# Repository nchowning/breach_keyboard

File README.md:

# Breach Split Keyboard

This is a hobby project to create a keyboard that fits my needs. I figured why not share my progress.

## Firmware

On this, I took the lazy way out after finding an online firmware builder - [Keyboard Firmware Builder](http://kbfirmware.com/). This thing is awesome. You point it at a [keyboard-layout-editor.com](https://www.keyboard-layout-editor.com) layout, tweak the settings, then it spits out a compiled .hex file (or the [qmk](https://qmk.fm) source if you want). In this repo, I'm including the keyboard-layout-editor json file as well as the Keyboard Firmware Builder config json file. You can just upload that config & have Keyboard Firmware Builder deliver a hex file for you. In the future I might include the qmk source in this repo but I won't bother for now.

Since this keyboard uses a pro micro for each half, the firmware flashing process is a little bit different than if you'd used a teensy 2.0. I've added a reset tact switch so that you can easily program it. Just quickly hit the reset button twice & then fire off something like this:

```
avrdude -p atmega32u4 -P /dev/ttyACM0  -c avr109 -U flash:w:breach-left.hex
```

`/dev/ttyACM0` might be different on your machine so keep that in mind.

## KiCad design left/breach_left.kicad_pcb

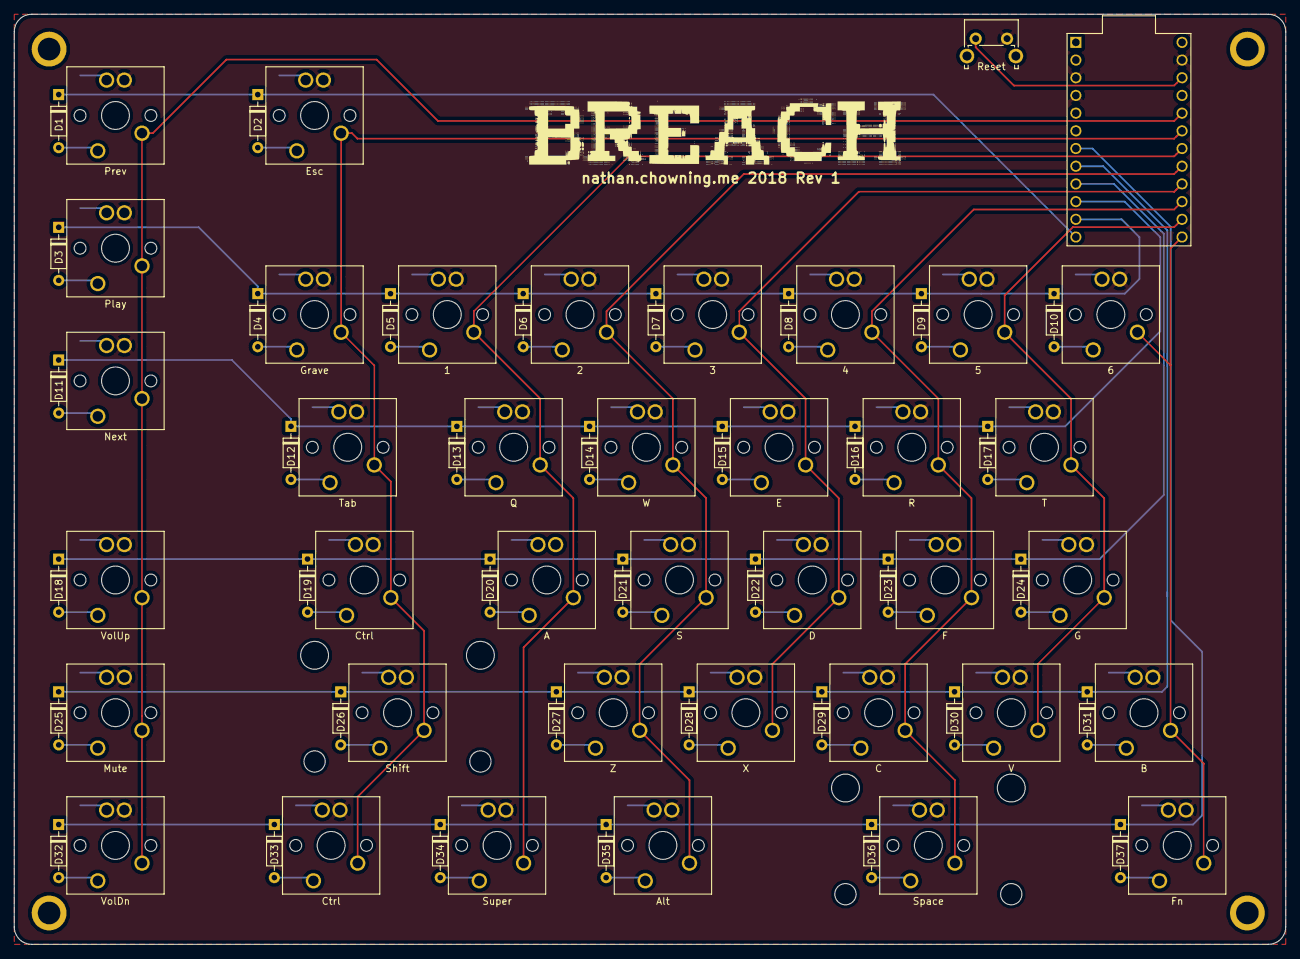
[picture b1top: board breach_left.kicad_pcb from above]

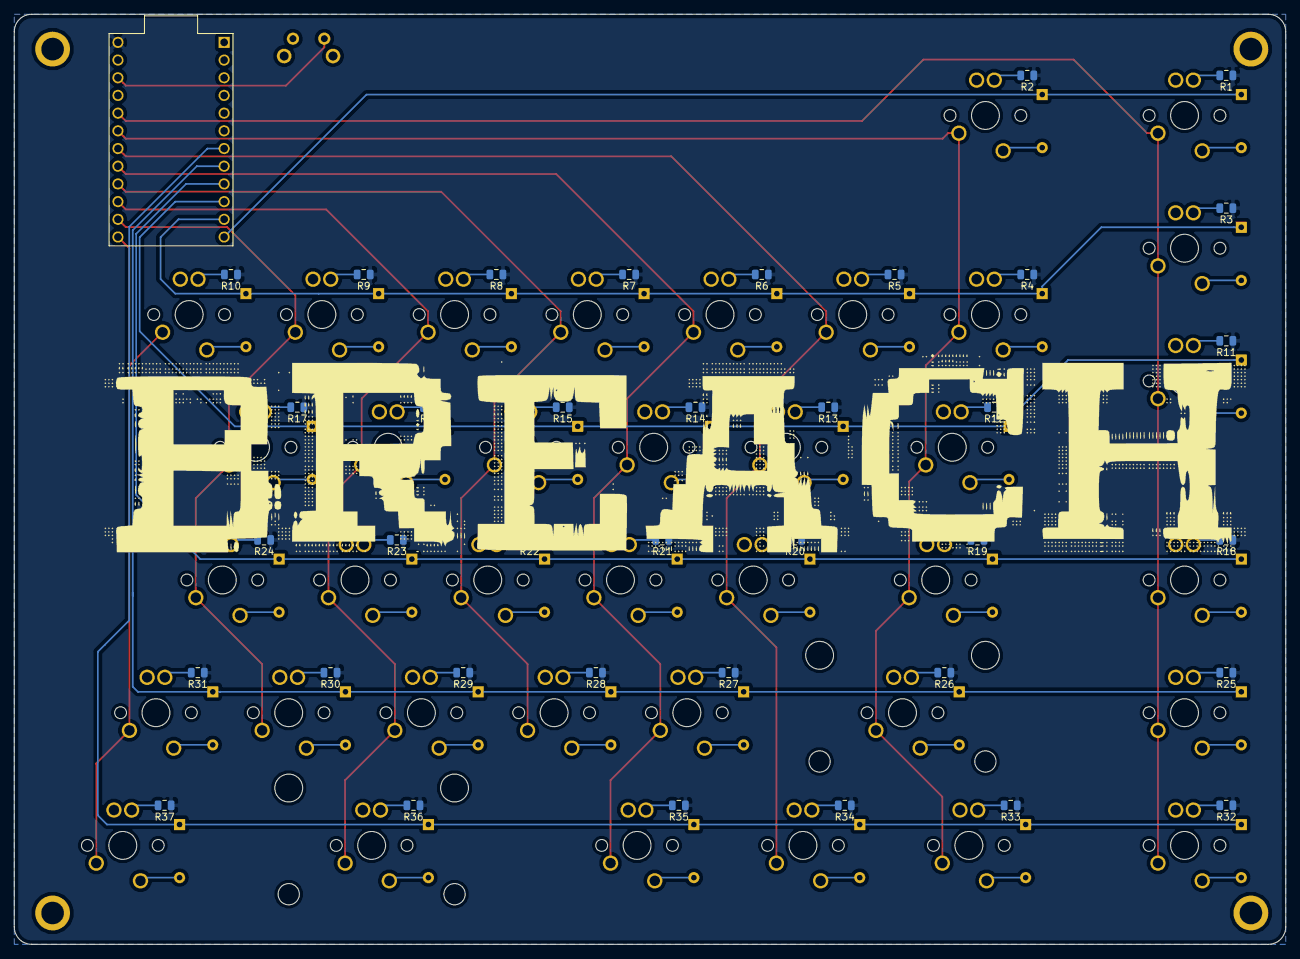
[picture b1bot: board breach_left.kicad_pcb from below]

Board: 2 copper layers, 182.5 x 133.5 mm, 113 parts (37 on the bottom side), 91 nets.

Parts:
D1, D2, D3, D4, D5, D6, D7, D8, D9, D10, D11, D12, D13, D14, D15, D16, D17, D18, D19, D20, D21, D22, D23, D24, D25, D26, D27, D28, D29, D30, D31, D32, D33, D34, D35, D36, D37: 1N4148; D_DO-35_SOD27_P7.62mm_Horizontal
R1, R2, R3, R4, R5, R6, R7, R8, R9, R10, R11, R12, R13, R14, R15, R16, R17, R18, R19, R20, R21, R22, R23, R24, R25, R26, R27, R28, R29, R30, R31, R32, R33, R34, R35, R36, R37: R_Small_US; R_0805_2012Metric
SW1, SW2, SW3, SW4, SW5, SW6, SW7, SW8, SW9, SW10, SW11, SW12, SW13, SW14, SW15, SW16, SW17, SW18, SW19, SW20, SW21, SW22, SW23, SW24, SW25, SW27, SW28, SW29, SW30, SW31, SW32, SW33, SW34, SW35, SW37: SW_Push_LED; SW_Cherry_MX1A_1.00u_PCB
SW26: SW_Push_LED; SW_Cherry_MX1A_2.25u_PCB
SW36: SW_Push_LED; SW_Cherry_MX1A_2.75u_PCB
SW38: SW_Push; SW_Tactile_SPST_Angled_PTS645Vx39-2LFS
U1: ProMicro

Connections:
5V: R1.1, R2.1, R3.1, R4.1, R5.1, R6.1, R7.1, R8.1, R9.1, R10.1, R11.1, R12.1, R13.1, R14.1, R15.1, R16.1, R17.1, R18.1, R19.1, R20.1, R21.1, R22.1, R23.1, R24.1, R25.1, R26.1, R27.1, R28.1, R29.1, R30.1, R31.1, R32.1, R33.1, R34.1, R35.1, R36.1, R37.1, U1.24
COL1: SW1.2, SW3.2, SW11.2, SW18.2, SW25.2, SW32.2, U1.20
COL2: SW2.2, SW4.2, SW12.2, SW19.2, SW26.2, SW33.2, U1.19
COL3: SW5.2, SW13.2, SW20.2, SW34.2, U1.18
COL4: SW6.2, SW14.2, SW21.2, SW27.2, SW35.2, U1.17
COL5: SW7.2, SW15.2, SW22.2, SW28.2, U1.16
COL6: SW8.2, SW16.2, SW23.2, SW29.2, SW36.2, U1.15
COL7: SW9.2, SW17.2, SW24.2, SW30.2, U1.14
COL8: SW10.2, SW31.2, SW37.2, U1.13
GND: SW1.3, SW2.3, SW3.3, SW4.3, SW5.3, SW6.3, SW7.3, SW8.3, SW9.3, SW10.3, SW11.3, SW12.3, SW13.3, SW14.3, SW15.3, SW16.3, SW17.3, SW18.3, SW19.3, SW21.3, SW22.3, SW23.3, SW24.3, SW25.3, SW26.3, SW27.3, SW28.3, SW29.3, SW30.3, SW31.3, SW32.3, SW33.3, SW34.3, SW35.3, SW36.3, SW37.3, SW38.2, U1.3, U1.4, U1.23
unnamed: D1.2, SW1.1
unnamed: D2.2, SW2.1
unnamed: D3.2, SW3.1
unnamed: D4.2, SW4.1
unnamed: D5.2, SW5.1
unnamed: D6.2, SW6.1
unnamed: D7.2, SW7.1
unnamed: D8.2, SW8.1
unnamed: D9.2, SW9.1
unnamed: D10.2, SW10.1
unnamed: D11.2, SW11.1
unnamed: D12.2, SW12.1
unnamed: D13.2, SW13.1
unnamed: D14.2, SW14.1
unnamed: D15.2, SW15.1
unnamed: D16.2, SW16.1
unnamed: D17.2, SW17.1
unnamed: D18.2, SW18.1
unnamed: D19.2, SW19.1
unnamed: D20.2, SW20.1
unnamed: D21.2, SW21.1
unnamed: D22.2, SW22.1
unnamed: D23.2, SW23.1
unnamed: D24.2, SW24.1
unnamed: D25.2, SW25.1
unnamed: D26.2, SW26.1
unnamed: D27.2, SW27.1
unnamed: D28.2, SW28.1
unnamed: D29.2, SW29.1
unnamed: D30.2, SW30.1
unnamed: D31.2, SW31.1
unnamed: D32.2, SW32.1
unnamed: D33.2, SW33.1
unnamed: D34.2, SW34.1
unnamed: D35.2, SW35.1
unnamed: D36.2, SW36.1
unnamed: D37.2, SW37.1
unnamed: R1.2, SW1.4
unnamed: R2.2, SW2.4
unnamed: R3.2, SW3.4
unnamed: R4.2, SW4.4
unnamed: R5.2, SW5.4
unnamed: R6.2, SW6.4
unnamed: R7.2, SW7.4
unnamed: R8.2, SW8.4
unnamed: R9.2, SW9.4
unnamed: R10.2, SW10.4
unnamed: R11.2, SW11.4
unnamed: R12.2, SW12.4
unnamed: R13.2, SW13.4
unnamed: R14.2, SW14.4
unnamed: R15.2, SW15.4
unnamed: R16.2, SW16.4
unnamed: R17.2, SW17.4
unnamed: R18.2, SW18.4
unnamed: R19.2, SW19.4
unnamed: R20.2, SW20.4
unnamed: R21.2, SW21.4
unnamed: R22.2, SW22.4
unnamed: R23.2, SW23.4
unnamed: R24.2, SW24.4
unnamed: R25.2, SW25.4
unnamed: R26.2, SW26.4
unnamed: R27.2, SW27.4
unnamed: R28.2, SW28.4
unnamed: R29.2, SW29.4
unnamed: R30.2, SW30.4
unnamed: R31.2, SW31.4
unnamed: R32.2, SW32.4
unnamed: R33.2, SW33.4
unnamed: R34.2, SW34.4
unnamed: R35.2, SW35.4
unnamed: R36.2, SW36.4
unnamed: R37.2, SW37.4
ROW1: D1.1, D2.1, U1.12
ROW2: D3.1, D4.1, D5.1, D6.1, D7.1, D8.1, D9.1, D10.1, U1.11
ROW3: D11.1, D12.1, D13.1, D14.1, D15.1, D16.1, D17.1, U1.10
ROW4: D18.1, D19.1, D20.1, D21.1, D22.1, D23.1, D24.1, U1.9
ROW5: D25.1, D26.1, D27.1, D28.1, D29.1, D30.1, D31.1, U1.8
ROW6: D32.1, D33.1, D34.1, D35.1, D36.1, D37.1, U1.7
RST: SW38.1, U1.22

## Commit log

2018-11-14 Renamed the project & pretty much finished the left side
2018-12-02 Lots of new changes here. Left side is usable
2018-12-03 Updated keyboard.py and removed keyboard grid picture
2018-12-04 Added layout & firmware configs and Readme
2018-12-04 Added flashing instructions
